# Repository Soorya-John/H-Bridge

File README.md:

# H-Bridge
An H bridge pcb made in Ki-Cad

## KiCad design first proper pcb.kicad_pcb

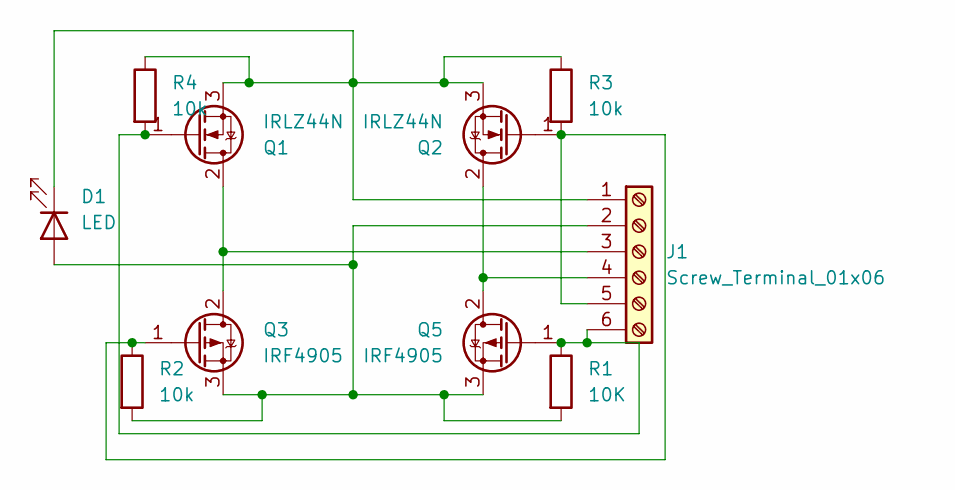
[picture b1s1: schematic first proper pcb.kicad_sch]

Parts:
D1: LED; LED_D5.0mm_Clear
J1: Screw_Terminal_01x06; TerminalBlock_4Ucon_1x06_P3.50mm_Horizontal
Q1, Q2: IRLZ44N; TO-220-3_Vertical
Q3, Q5: IRF4905; TO-220-3_Vertical
R1: 10K; R_Axial_DIN0207_L6.3mm_D2.5mm_P10.16mm_Horizontal
R2, R3, R4: 10k; R_Axial_DIN0207_L6.3mm_D2.5mm_P10.16mm_Horizontal

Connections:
unnamed: D1.2 (A), J1.2, Q3.3 (S), Q5.3 (S), R1.2, R2.2
unnamed: D1.1 (K), J1.1, Q1.3 (S), Q2.3 (S), R3.1, R4.1
unnamed: J1.3, Q1.2 (D), Q3.2 (D)
unnamed: J1.4, Q2.2 (D), Q5.2 (D)
unnamed: J1.5, Q2.1 (G), Q3.1 (G), R2.1, R3.2
unnamed: J1.6, Q1.1 (G), Q5.1 (G), R1.1, R4.2

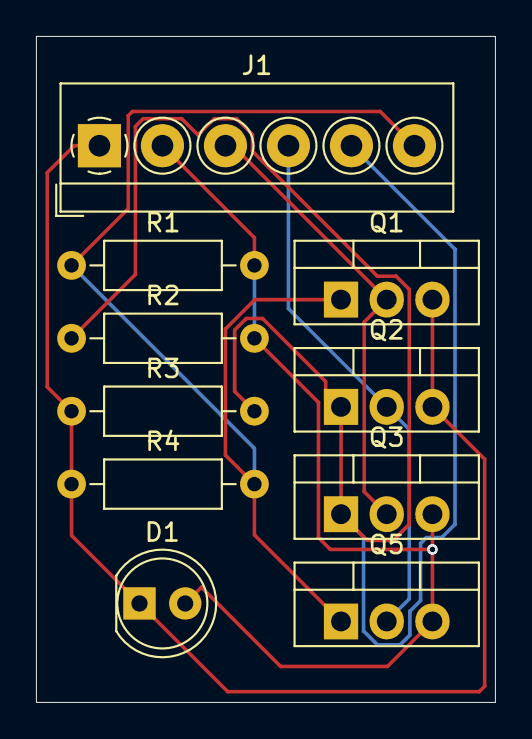
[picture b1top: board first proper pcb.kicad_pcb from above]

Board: 2 copper layers, 25.5 x 37.0 mm, 10 parts (0 on the bottom side), 6 nets.
